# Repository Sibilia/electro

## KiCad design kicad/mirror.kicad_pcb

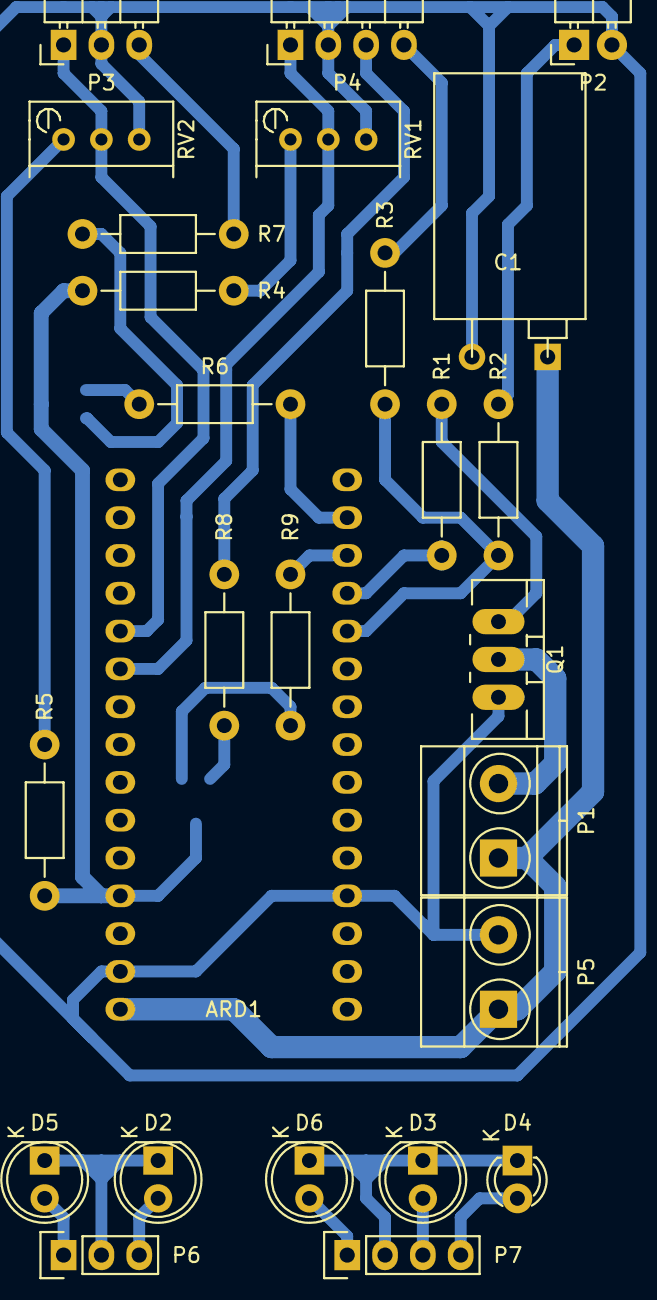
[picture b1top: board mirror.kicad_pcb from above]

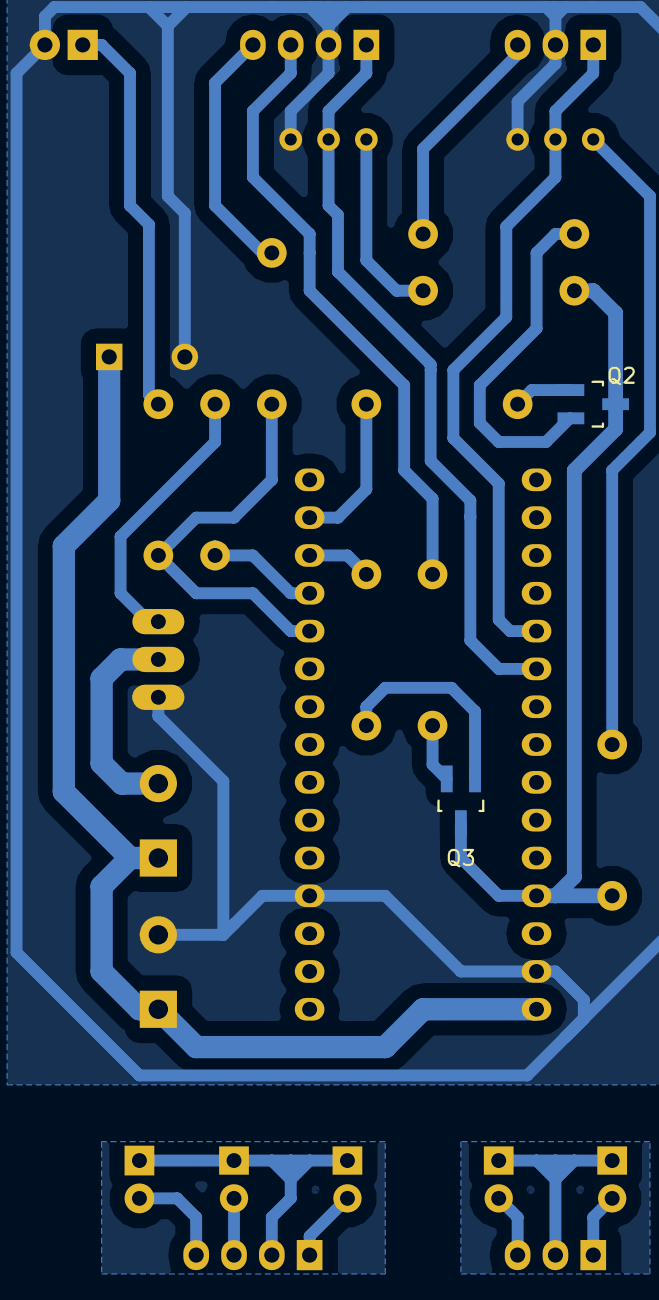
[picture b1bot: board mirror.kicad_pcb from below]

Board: 2 copper layers, 28 parts (2 on the bottom side), 28 nets.

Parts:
ARD1: arduino_nano
C1: 1000uF; CPR10X16
D2, D3: IR_LED; LED-5MM
D4: LED; LED-3MM
D5, D6: FOTO_DIOD; LED-5MM
P1, P5: CONN_01X02; TerminalBlock_Pheonix_MKDS1.5-2pol
P2: CONN_01X02; Pin_Header_Angled_1x02
P3: CONN_01X03; Pin_Header_Angled_1x03
P4: CONN_01X04; Pin_Header_Angled_1x04
P6: CONN_01X03; Pin_Header_Straight_1x03
P7: CONN_01X04; Pin_Header_Straight_1x04
Q1: IRLZ44N; TO-220_Neutral123_Vertical_LargePads
Q2, Q3: Q_NPN; SOT-23_Handsoldering
R1: 100; Resistor_Horizontal_RM10mm
R2, R3: 220; Resistor_Horizontal_RM10mm
R4, R5, R6, R9: 1k; Resistor_Horizontal_RM10mm
R7, R8: 39; Resistor_Horizontal_RM10mm
RV1, RV2: 500k; Potentiometer_Bourns_3296W_3-8Zoll_Inline_ScrewUp

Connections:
+5V: ARD1.12, Q2.3, Q3.3, R4.2, R5.2
+12V: ARD1.15, C1.1, P1.1, P5.1
GND: ARD1.14, ARD1.19, C1.2, P2.2, P3.2, P4.2, P5.2, Q1.3, RV1.3, RV2.3
unnamed: ARD1.5, P3.1, RV2.2
unnamed: ARD1.6, P4.1, RV1.2
unnamed: ARD1.26, R2.1, R3.2
unnamed: ARD1.27, R1.2
unnamed: ARD1.28, R9.2
unnamed: ARD1.29, R6.2
unnamed: D2.1, D5.1, P6.2
unnamed: D2.2, P6.3
unnamed: D3.1, D4.1, D6.1, P7.2
unnamed: D3.2, P7.3
unnamed: D4.2, P7.4
unnamed: D5.2, P6.1
unnamed: D6.2, P7.1
unnamed: P1.2, Q1.2
unnamed: P2.1, R2.2
unnamed: P3.3, R7.1
unnamed: P4.3, R8.2
unnamed: P4.4, R3.1
unnamed: Q1.1, R1.1
unnamed: Q2.1, R6.1
unnamed: Q2.2, R7.2
unnamed: Q3.1, R9.1
unnamed: Q3.2, R8.1
unnamed: R4.1, RV1.1
unnamed: R5.1, RV2.1

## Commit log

2017-08-10 add arduino cketch and kicad
2017-08-10 move to mirror dir
